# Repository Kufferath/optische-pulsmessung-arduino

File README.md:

# optische-pulsmessung-arduino
Optische Pulsmessung mit Arduino und Ausgabe via Nextion Display

In diesem Projekt wir beschrieben , wie man mit Hilfe einer Infrarot-Led und einer Photodiode auf optischem Wege eine Pulsmessung durchführen kann.
Als Basis dient ein Arduino UNO und die Ausgabe erfolgt mit einem Nextion Display.
Als Hardware ist ein Messvertärker erforderlich, der eine Bandpassfunktion aufweist.
Schaltplan und weitere Infos sind hier hinterlegt.

Zum Nachbau des Projekts sind folgende Schritte nötig:

 - Aufbau des Messverstärkers
 - Montage der LED und der Photodiode
 - Programmierung des  Arduino UNO
 - Gestaltung des Layouts für das Nextion Display
 - Verdrahten der Komponenten

Sie finden die nötigen Dateien im Verzeichnis

##Hinweis

>Von besonderem Interesse mag die Einbindung des
>Nextion Displays sein, da es über Serielle Befehle
>zu steuern ist und den Prozessor zur Laufzeit nicht 
>belastet.
>Mit Hilfe des Desktop-Editors von Nextion , ist eine
>einfache Gestaltung des Layouts möglich.

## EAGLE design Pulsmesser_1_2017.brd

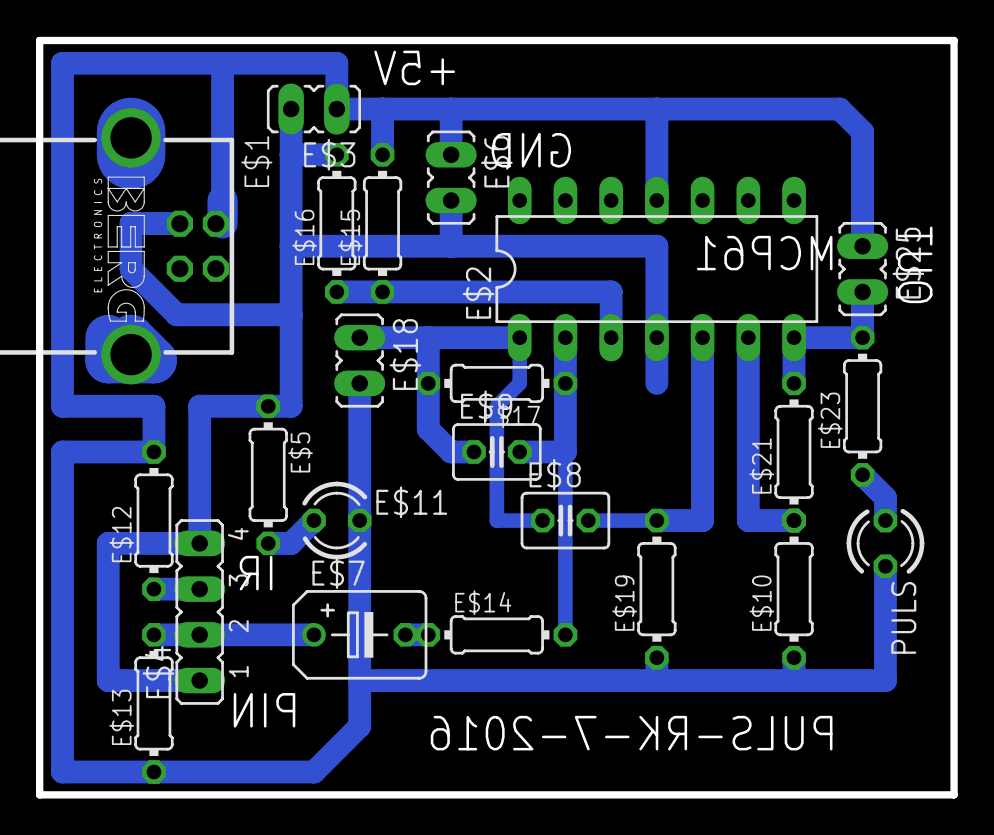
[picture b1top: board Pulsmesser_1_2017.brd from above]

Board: 2 copper layers, 50.8 x 41.9 mm, 23 parts (0 on the bottom side), 13 nets.

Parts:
E$1: PN61729-S
E$2: MCP6144; DIL14
E$3, E$6, E$18, E$25: JP1Y
E$4: JP4
E$5: 470R; 0204/7
E$7: B45181B
E$8: C025-030X050
E$9: 2,2nF; C025-030X050
E$10: 2K2; 0204/7
E$11: LED3MM
E$12: 120R; 0204/7
E$13: 50K; 0204/7
E$14: 150K; 0204/7
E$15, E$16: 220K; 0204/7
E$17: 3,3M; 0204/7
E$19: 4,7M; 0204/7
E$21: 10K; 0204/7
E$23: 220R; 0204/7
PULS: LED3MM

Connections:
S$1: E$2.3, E$16.1
S$2: E$2.4, E$3.2, E$4.1, E$4.4, E$6.2, E$16.2
S$3: E$4.3, E$12.1
S$4: E$4.2, E$7.+, E$13.2
S$6: E$7.-, E$14.1
S$7: E$2.2, E$9.2, E$14.2
S$10: E$2.1, E$8.1, E$9.1, E$17.2, E$18.1
S$11: E$2.5, E$8.2
S$13: E$2.6, E$21.1
S$14: E$2.7, E$21.2, E$23.2, E$25.2
S$16: E$23.1, PULS.A
S$18: E$2.11, E$3.1, E$6.1, E$10.1, E$12.2, E$13.1, E$15.2, E$18.2, E$19.1, E$25.1, PULS.K
S$19: E$5.2, E$11.A

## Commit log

2017-01-05 Einführung in das Projekt - 1 -2017
2017-01-05 aktuelle Files hochgeladen
2017-01-05 file2upload
2017-01-05 Update_2
2017-01-05 Nextion Display
